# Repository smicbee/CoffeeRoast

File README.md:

# CoffeeRoast

We built a coffee roaster from a popcorn machine by adding temperature control. It follows a reproducible roast curve.

## Used Components

**Microcontroller:** LilyGo T-Display S3 ESP32-S3 (probably overkill, but it has a nice display and WiFi functionality if needed)  
From: [Amazon](https://www.amazon.de/LILYGO-T-Display-S3-Entwicklungsboard-Normalbildschirm-schwarzem/dp/B0BRTT727Z?source=ps-sl-shoppingads-lpcontext&ref_=fplfs&smid=ANWK9D8XV9DLB&th=1)

**Popcorn Maker:** [Severin Popcorn-Maker](https://popcorn-rezepte.de/severin-pc-3751-popcornautomat-weiss-heissluft)  
From: Ebay/Kleinanzeigen for 5-10€. People often get this as a gift, use it once or not at all, and then sell it on eBay.

**Temperature Sensor:** MAX6675 Temperature Sensor, K Type  
From: [Amazon](https://www.amazon.de/dp/B0DFM7SJ3Z?ref=ppx_yo2ov_dt_b_fed_asin_title)

**Solid State Relay:** Solid-State-Relay SSR-40DA  
From: [Amazon](https://www.amazon.de/dp/B0CDKCBJRT?ref=ppx_yo2ov_dt_b_fed_asin_title)

Cables, drills, screwdriver, soldering iron

## Instructions

To modify the roaster, we had to:
* Add a temperature sensor
* Add a solid-state relay to the heater
* Add a PWM transistor to the fan

First, we took apart the popcorn maker. It basically consists of two elements: heating coils and a fan for the air.  
These popcorn makers are engineered to the limit, so please be gentle with them as they are made of a lot of plastic. We destroyed a couple until we got it right. Even then, the plastic melted on the third continuous roast.

The main power switch connects the 230V from the outlet directly to the heating coils. The fan is connected to the heating coil in a way that ~24V AC goes through a rectifier (4 diodes) and is converted from AC to DC.

In the first step, we needed to decouple the heating coils from the fan and make the heating coil controllable using our solid-state relay. We disconnected the fan from the diodes so we could run it from an external power supply providing 24V later on.  
The heating coil was then soldered directly to the neutral conductor (blue wire). The red wire was cut, and the solid-state relay was installed in between so we could control the power of the heating element using PWM later.

An external or lab power supply was used to provide 24V DC to the fan, so it runs permanently. The fan can take from 4V to 30V. We can adjust the voltage to control the speed or later use a GPIO, a diode, and a transistor to control it from the ESP32. The ESP ensures a smooth start of the fan. We broke one of the fans due to rapid spin up/down.

We drilled a hole in the top metal container to fit the thermocouple inside the roasting chamber.  
**Note:** If the temperature sensor touches the metal casing, it won't work properly. We insulated the sensor with Kapton tape or a non-conductive washer. The temperature reading is 0°C if the motor is spinning and no insulation was used. This is handled by the code to be filtered out, but the roaster will go into fail-safe mode after 30s of nonsensical temperature readings and spin up the fan to 100%.

The other 4 pins go into the ESP32 (VCC = 5V, GND = Ground, CLK = GPIO_13, CS = GPIO_12, DO = GPIO_11).

Also, the solid-state relay is connected to the ESP32. In our case, the voltage provided by the GPIO was sufficient to control the solid-state relay, so we controlled it directly via the GPIO. If this does not work, you will need a separate transistor and a 5V supply for the SSR.  
The SSR uses GPIO_1 in our setup.

## Control Box

We 3D printed a box containing:
* ESP32
* 24V Fan PWM control
* SSR (solid-state relay) control
* Temperature sensor readout board

And that's it!

Initially, we wanted to use the ESP32 with Artisan (the software used for commercial products, e.g., Coffeelogic Nano), but we had no luck getting it to work with a PID. So, we decided to write our own software using C#. Communication is done via simple serial commands.  
You can send "get temp" via serial to the ESP32, and it will respond with the current temperature from the thermocouple.  
You can also send "set setpoint 255", which the ESP32 interprets to set the PWM duty cycle to 100% (255 = 100%, 128 = 50%, 0 = 0%).  
The firmware clamps `set setpoint` and `set fan` commands to the 0-255 PWM range and supports `get status` for a compact controller health line with state, temperature, heater, fan, fan target, and thermocouple error count.
The C# application can be found in the iRoastControl folder.

# Example Usage

Use no more than 100g of beans and roast in a well-ventilated area. Prepare for coffee skins flying _everywhere_.  
You can stop the roast at any time by flipping the on-off switch, which effectively disconnects the heater while keeping the cooling fan running.

[12s_roast.webm](https://github.com/user-attachments/assets/c60a7ab9-1068-4cd1-9d56-9880ee272cc1)

[12s video of 12min roasting](docu/assets/img/rel/12s_roast.webm)

# CoffeeRoast V2 Web

Die neue Steuerungsoberfläche liegt unter [`CoffeeRoast V2/`](CoffeeRoast%20V2/) und ist als moderne, responsive Webanwendung umgesetzt.

- Live-Verbindung zum bestehenden ESP32 über die Web Serial API
- vorhandenes serielles Protokoll und alle `.kpro`-Rezepte bleiben nutzbar
- Safety-Preflight, Failsafe, Vorheizen, Rösten und Abkühlen
- eingebauter Simulator, Canvas-Live-Plot und CSV-Export
- öffentlich bereitgestellt unter **https://coffeeroast.michaelbeetz.de/**

Für die USB-Verbindung wird Chrome oder Edge benötigt. Der Browser spricht direkt mit dem lokal ausgewählten USB-Gerät; der Webserver erhält keinen Zugriff auf den Controller.

# iRoastControl (Legacy)

iRoastControl is the control software. It comes with predefined roast curves you can use for your first roast.

## Build and Run on Windows

iRoastControl is a Windows Forms application for .NET Framework 4.7.2. Build it with Visual Studio 2022 and the ".NET desktop development" workload installed, including the .NET Framework 4.7.2 targeting pack or developer pack.

1. Connect the ESP32 roaster controller to the Windows PC over USB and confirm it appears as a COM port.
2. Open `iRoastControl Software/iRoastControl.sln` in Visual Studio.
3. Restore NuGet packages when Visual Studio prompts you, or use **Build > Restore NuGet Packages** before the first build. The project uses `packages.config`, so packages are restored into a repository-level `packages` folder.
4. Build the `Debug|Any CPU` or `Release|Any CPU` configuration, then press **Start** in Visual Studio or run the generated `iRoastControl.exe` from `iRoastControl Software/bin/Debug/` or `iRoastControl Software/bin/Release/`.

On startup the application scans available COM ports at `115200` baud, 8 data bits, no parity, one stop bit, and no handshake. It sends `hello` and expects the ESP32 firmware to answer `popcorn roaster`; after that it sends commands such as `get temp`, `set setpoint <0-255>`, and `set fan <0-255>`. If the app does not connect, check that the ESP32 firmware is running, no serial monitor has the port open, and the USB driver exposes the board as a COM port.

Roast recipes are loaded from the `Recipes` folder next to the running application. The source recipes live in `iRoastControl Software/Recipes/*.kpro` and are copied to the build output during the Visual Studio build. Add custom `.kpro` files to that folder before building, or copy them into `bin/Debug/Recipes/` or `bin/Release/Recipes/` beside the executable.

## First-Run Calibration and Safety Check

Before the first heated run, flash the ESP32 firmware, start iRoastControl, and leave the chamber empty. When you press "Run" from idle, the application requests `get status` from the controller and shows a preflight checklist. Confirm only after the thermocouple is insulated from the metal chamber, the fan moves air freely, the SSR is wired through the controller, ventilation is running, and the manual power cut-off is reachable.

Each roasting curve has three phases: pre-heating, running, and cool-down. When you click "Run" the first time, the application pre-heats the empty popcorn machine until the thermocouple reaches 180°C. This is when you add your coffee beans. After that, press "Run" again and the button will turn yellow. This is where the roasting curve starts. You can follow your roasting temperatures by watching the red graph. Pressing the "Run" button again will abort and start the cool-down phase, where the heating element turns off and only the fan runs. When the temperature drops below 60°C, the app returns to idle.

If the thermocouple returns repeated impossible readings, the firmware enters failsafe, turns the heater off, and drives the fan to 255/255. The app also treats a controller status containing `failsafe` as a blocked start until the wiring or sensor issue is fixed.

## UI

At the moment, the curves are defined by some points in the source code, which get interpolated using a CubicSpline function. You can find the key points in `ControlClass.cs` in the function `generateDefaultCurve()`. Each point describes the temperature depending on the time in seconds, e.g., `targetPoints.Add(new PointF(660, 180));` means at 660s of the roasting curve, we should reach 180°C.  
Adjust as you like.

# Fails

If the popcorn maker is old (like 20 years), the fan blades are rather brittle and may break easily if used on full power.

**Note:** If the temperature sensor touches the metal casing, it won't work properly. We recommend insulating the sensor with Kapton tape or a non-conductive washer.

# Tips

* Cover any holes on top with Kapton tape to retain heat better. Plastic might melt a bit, though.
* Test the roast with actual popcorn, as it's cheaper if anything goes wrong.
* Experiment and change only one setting at a time.

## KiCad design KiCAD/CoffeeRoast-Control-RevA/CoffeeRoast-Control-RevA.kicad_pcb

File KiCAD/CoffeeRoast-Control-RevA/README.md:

# CoffeeRoast-Control RevA.1 PCB Draft

This is the generated RevA.1 hardware draft for moving the CoffeeRoast electronics onto a PCB. The current board has been updated with the agreed robustness optimizations and has zero KiCad error-level DRC violations, but it still needs manual engineering review before fabrication.

## Design decision captured from chat

- Use **one 230V appliance inlet for the whole roaster enclosure**.
- Inside the enclosure use a **certified isolated 230VAC -> 24VDC / 3A PSU**.
- The controller PCB itself is **low-voltage only** and accepts the PSU's 24VDC output.
- The PCB generates 5V via a buck module and 3.3V via a RevA.1 switching-regulator footprint/selection for the ESP32-S3 module.
- The heater's 230V path is still switched by an **external SSR module with heatsink**; 230V is intentionally not routed on this PCB.
- RevA.1 adds low-voltage robustness features: input bulk capacitor, 24V input TVS, fan TVS, USB ESD footprint, thermocouple filter footprint, and rail test pads.

## Files

- `CoffeeRoast-Control-RevA.kicad_pcb` — KiCad board draft with real on-board USB-C footprint and autorouted/manual-cleanup tracks.
- `CoffeeRoast-Control-RevA.kicad_sch` — vollständiger, editierbarer KiCad-Schaltplan mit Funktionsblöcken für Versorgung, Lüfter/SSR, ESP32, MAX6675, USB und Testzugänge; die benannten Netze entsprechen dem gerouteten PCB.
- `tools/generate_full_schematic.py` — reproduzierbarer Generator für den Schaltplanentwurf; die native `.kicad_sch`-Datei wurde mit KiCad 9 konvertiert und geprüft.
- `render/schematic/CoffeeRoast-Control-RevA.pdf` und `.svg` — exportierte Schaltplanansichten; `render/schematic/erc.json` enthält den aktuellen ERC-Bericht.
- `docs/netlist.csv` — tabellarische Referenz der beabsichtigten elektrischen Verbindungen.
- `docs/bom.csv` — Stückliste des aktuellen PCB-Entwurfs.
- `docs/esp32_debug_pads.csv` — ESP32-S3 TPESP1-40 tiny probe pad mapping.
- `docs/esp32_solder_pads.csv` — larger labeled bottom-side PADESP1-40 solder pad mapping for attaching wires later.
- `docs/routing_notes.md` — routing/DRC status and fabrication caveats.
- `docs/reva1_optimizations.md` — RevA.1 robustness changes and what was deliberately left for RevB.
- `tools/apply_reva1_optimizations.py` — idempotent pcbnew script that applies the RevA.1 PCB additions.
- `production/partial-smd-pcba/` — generated Gerber/drill + partial SMD assembly BOM/CPL package for first prototype ordering.
- `tools/prepare_partial_pcba_package.py` — regenerates the partial-SMD PCBA handoff package.
- `symbols/` and `footprints.pretty/` — local ESP32-S3-WROOM-1 and USB-C library files copied from KiCad upstream.

## Firmware pin mapping preserved

| Function | ESP32-S3-WROOM-1 pin | GPIO | Firmware variable |
|---|---:|---:|---|
| Heater/SSR PWM | 39 | GPIO1 | `relayPin` |
| Fan PWM | 38 | GPIO2 | `fanPin` |
| MAX6675 DO/SO | 19 | GPIO11 | `thermoDO` |
| MAX6675 CS | 20 | GPIO12 | `thermoCS` |
| MAX6675 CLK/SCK | 21 | GPIO13 | `thermoCLK` |
| USB D- | 13 | native USB D- | serial/flash |
| USB D+ | 14 | native USB D+ | serial/flash |
| BOOT | 27 | GPIO0 | flash mode |
| EN/RESET | 3 | EN | reset |

## ESP32 debug pads

All ESP32-S3-WROOM-1 side pins 1-40 are exposed twice: tiny local probe pads named `TPESP1` through `TPESP40` around U1, and larger labeled bottom-side solder pads named `PADESP1` through `PADESP40` routed outward for attaching wires later. The mappings are in `docs/esp32_debug_pads.csv` and `docs/esp32_solder_pads.csv`. These include the spare GPIOs plus already-used signals such as USB D+/D-, MAX6675 SPI, BOOT/EN, fan PWM, heater/SSR PWM, 3V3, and GND.

## Power tree

```text
230VAC inlet in enclosure
  +--> certified 230VAC -> 24VDC / 3A PSU
          +--> J1 on this PCB
                +--> C4 input bulk + D2 24V TVS protection
                +--> F1 24V-side fuse placeholder
                +--> J2 24V fan via Q1 low-side MOSFET + D1/D3 fan clamp
                +--> U4 24V -> 5V buck module
                        +--> SSR input driver supply
                        +--> U3 3.3V switching regulator selection
                                +--> ESP32-S3-WROOM-1 + MAX6675

230VAC heater line: external SSR module only, not on this PCB.
```

## Important limitations before fabrication

This board now loads in KiCad 9 and has been routed/checked headlessly. KiCad error-level DRC is clean, but before ordering boards:

1. Open the project in KiCad.
2. Replace remaining generic placeholders with exact sourced parts: fuse holder, U3 switching regulator footprint, U4 buck module, TVS packages, USB ESD package, MOSFET/regulator variants. J1-J4 are deliberately large hand-solder pads now, not PCBA connector placements.
3. Re-run ERC/DRC after any mechanical/footprint changes.
4. Confirm ESP32-S3-WROOM-1 antenna keepout has no copper and is at board edge.
5. Confirm the fan path, D3 TVS choice, Q1 MOSFET, and hand-solder pad/wire strain-relief scheme are rated for the real 24V/2.5A fan current.
6. Confirm J5 enclosure cutout/edge placement for the exact USB-C part and replace U5 with an exact USB2 ESD footprint.
7. Review USB CC pulldowns: R10/R11 = 5.1k to GND, VBUS is sense-only.
8. Decide whether C5 should be populated after thermocouple noise testing; leave DNP if it biases readings.
9. Review mains wiring separately: fused IEC inlet, PE/strain relief, certified 24V PSU, external SSR heatsink, thermal cut-off.

## RevB candidates

- Replace the generic U4 buck module with an integrated switch-mode converter.
- Add reverse-polarity ideal-diode/P-MOSFET input protection if final wiring risk justifies the extra footprint/reroute.
- Add current/thermal sensing for fan/heater diagnostics.

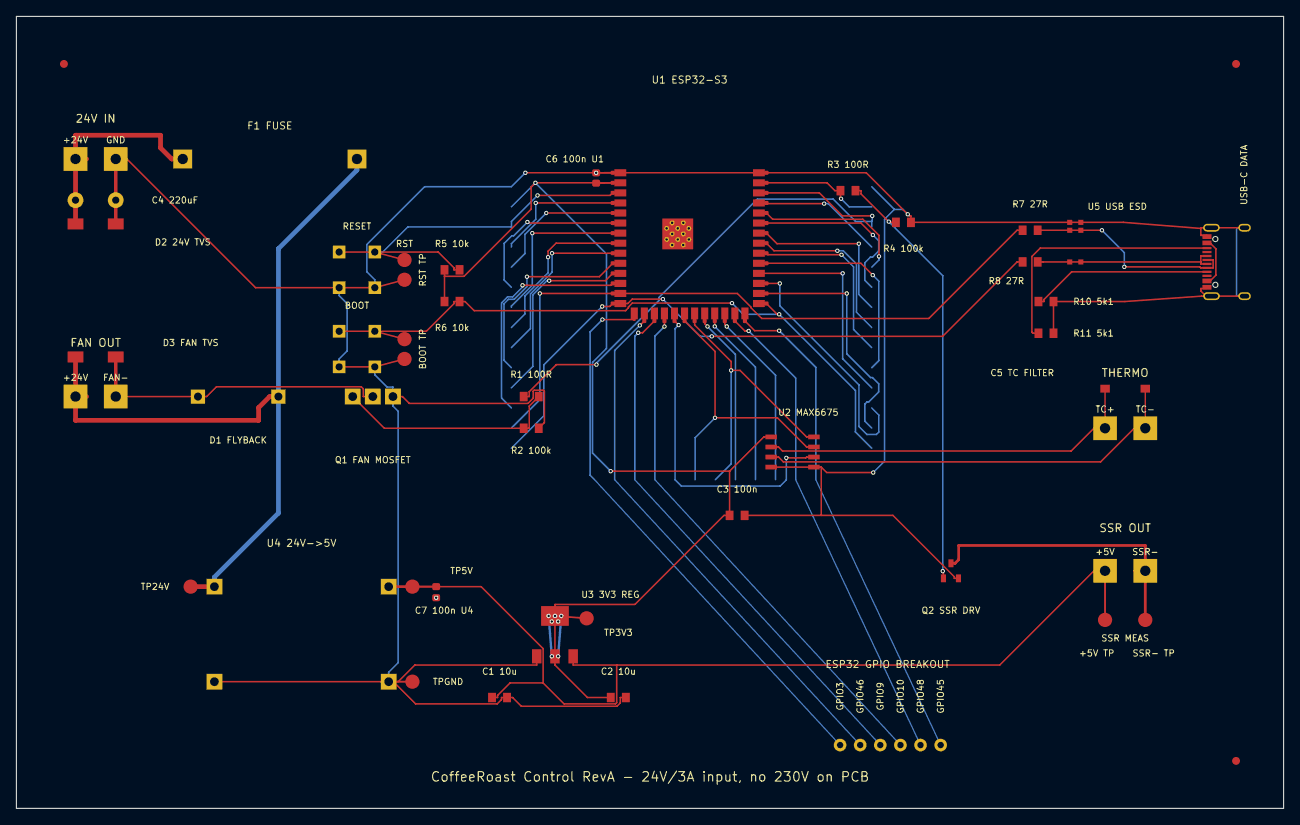
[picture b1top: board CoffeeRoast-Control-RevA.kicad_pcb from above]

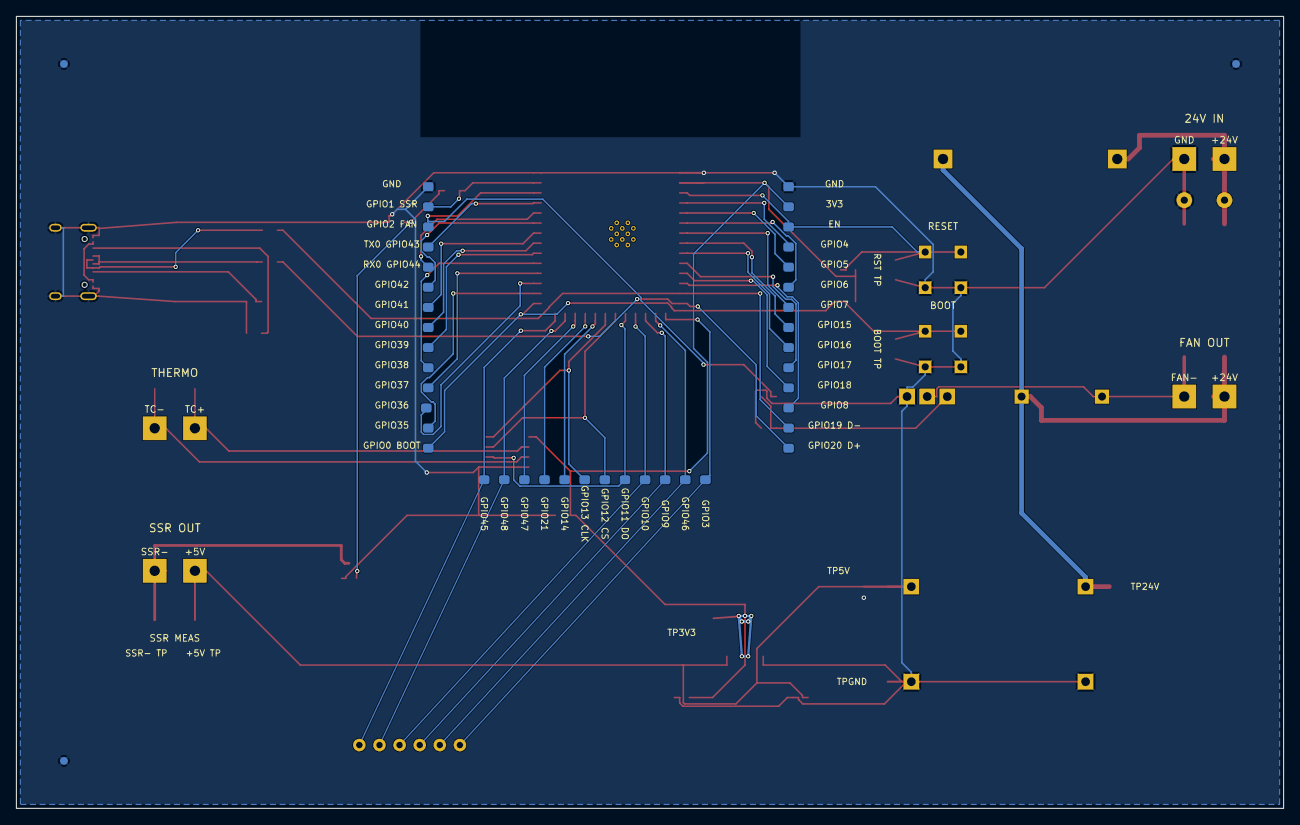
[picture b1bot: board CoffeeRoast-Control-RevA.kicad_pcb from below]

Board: 2 copper layers, 160.0 x 100.0 mm, 129 parts (43 on the bottom side), 53 nets.

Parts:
C1: 10uF_5V
C2: 10uF_3V3
C3: 100nF_MAX6675
C4: 220uF_35V_INPUT_BULK
C5: 1nF_C0G_THERMO_DIFF_FILTER_DNP_IF_NOISY
C6: 100nF_U1_DECOUPLING_0603
C7: 100nF_U4_OUTPUT_DECOUPLING_0603
D1: SB560_FLYBACK
D2: SMBJ33A_24V_INPUT_TVS
D3: SMBJ33A_FAN_TVS
F1: T3.15A_24V_SIDE
FID1, FID2, FID3, FID4, FID5, FID6: FIDUCIAL_GLOBAL_1MM
J1: 24V_IN_FROM_230V_PSU_3A
J2: FAN_24V_PWM_3A
J3: SSR_INPUT_TO_EXTERNAL_SSR
J4: K_TYPE_THERMOCOUPLE
J5: USB_C_Receptacle_XKB_U262-16XN-4BVC11
JGPIO1: ESP32_GPIO_BREAKOUT_ROW
PADESP1, PADESP40: GND
PADESP2: 3V3
PADESP3: EN
PADESP4: IO4
PADESP5: IO5
PADESP6: IO6
PADESP7: IO7
PADESP8: IO15
PADESP9: IO16
PADESP10: IO17
PADESP11: IO18
PADESP12: IO8
PADESP13: USB_D-
PADESP14: USB_D+
PADESP15: IO3
PADESP16: IO46
PADESP17: IO9
PADESP18: IO10
PADESP19: IO11
PADESP20: IO12
PADESP21: IO13
PADESP22: IO14
PADESP23: IO21
PADESP24: IO47
PADESP25: IO48
PADESP26: IO45
PADESP27: IO0
PADESP28: IO35
PADESP29: IO36
PADESP30: IO37
PADESP31: IO38
PADESP32: IO39
PADESP33: IO40
PADESP34: IO41
PADESP35: IO42
PADESP36: RXD0
PADESP37: TXD0
PADESP38: IO2
PADESP39: IO1
Q1: IRLB8721_OR_3V3_LOGIC_NMOS_RDS_ON_LOW
Q2: 2N7002_SSR_DRIVER
R1, R3: 100R
R2, R4: 100k
R5: 10k_EN_PULLUP
R6: 10k_BOOT_PULLUP
R7: 27R_USB_DN
R8: 27R_USB_DP
R10: 5k1_CC1_RD
R11: 5k1_CC2_RD
SW1: RESET_EN
SW2: BOOT
TP3V3: +3V3_TEST
TP5V: +5V_TEST
TP24V: +24V_FUSED_TEST
TPBOOT1: BOOT_TWEEZER_PADS
TPESP1, TPESP40: GND
TPESP2: 3V3
TPESP3: EN
TPESP4: IO4
TPESP5: IO5
TPESP6: IO6
TPESP7: IO7
TPESP8: IO15
TPESP9: IO16
TPESP10: IO17
TPESP11: IO18
TPESP12: IO8
TPESP13: USB_D-/IO19
TPESP14: USB_D+/IO20
TPESP15: IO3
TPESP16: IO46
TPESP17: IO9
TPESP18: IO10
TPESP19: IO11/MAXDO
TPESP20: IO12/MAXCS
TPESP21: IO13/MAXCLK
TPESP22: IO14
TPESP23: IO21
TPESP24: IO47
TPESP25: IO48
TPESP26: IO45
TPESP27: IO0/BOOT
TPESP28: IO35
TPESP29: IO36
TPESP30: IO37
TPESP31: IO38
TPESP32: IO39
TPESP33: IO40
TPESP34: IO41
TPESP35: IO42
TPESP36: RXD0/IO44
TPESP37: TXD0/IO43
TPESP38: IO2/FAN
TPESP39: IO1/SSR
TPGND: GND_TEST
TPRESET1: RESET_TWEEZER_PADS
TPSSR1: SSR_OUT_MEAS_PADS
U1: ESP32-S3-WROOM-1
U2: MAX6675_SOIC8_3V3
U3: 3V3_SWITCHING_REGULATOR_>=600mA_5V_IN_REPLACES_AM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
U4: 24V_TO_5V_BUCK_MODULE_>=1A_LOW_NOISE
U5: USBLC6-2SC6_OR_USB2_ESD

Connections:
+3V3: C2.1, C3.1, C6.1, PADESP2.1, R5.1, R6.1, TP3V3.1, TPESP2.1, U1.2, U2.4, U3.2
+5V: C1.1, C7.1, J3.1, TP5V.1, TPSSR1.1, U3.3, U4.3
+24V_FUSED: D1.2, D3.1, F1.2, J2.1, TP24V.1, U4.1
+24V_RAW: C4.1, D2.1, F1.1, J1.1
BOOT: PADESP27.1, R6.2, SW2.1, SW2.2, TPBOOT1.1, TPESP27.1, U1.27
EN: PADESP3.1, R5.2, SW1.1, SW1.2, TPESP3.1, TPRESET1.1, U1.3
FAN_GATE: Q1.1, R1.2, R2.1
FAN_NEG: D1.1, D3.2, J2.2, Q1.2
FAN_PWM: PADESP38.1, R1.1, TPESP38.1, U1.38
GND: C1.2, C2.2, C3.2, C4.2, C6.2, C7.2, D2.2, FID4.1, FID5.1, FID6.1, J1.2, J5.A1, J5.A12, J5.B1, J5.B12, J5.S1, PADESP1.1, PADESP40.1, Q1.3, Q2.2, R2.2, R4.2, R10.2, R11.2, SW1.3, SW1.4, SW2.3, SW2.4, TPBOOT1.2, TPESP1.1, TPESP40.1, TPGND.1, TPRESET1.2, U1.1, U1.40, U2.1, U2.8, U3.1, U4.2, U4.4, U5.3, U5.4
GPIO3: JGPIO1.1, PADESP15.1, TPESP15.1, U1.15
GPIO4: PADESP4.1, TPESP4.1, U1.4
GPIO5: PADESP5.1, TPESP5.1, U1.5
GPIO6: PADESP6.1, TPESP6.1, U1.6
GPIO7: PADESP7.1, TPESP7.1, U1.7
GPIO8: PADESP12.1, TPESP12.1, U1.12
GPIO9: JGPIO1.3, PADESP17.1, TPESP17.1, U1.17
GPIO10: JGPIO1.4, PADESP18.1, TPESP18.1, U1.18
GPIO14: PADESP22.1, TPESP22.1, U1.22
GPIO15: PADESP8.1, TPESP8.1, U1.8
GPIO16: PADESP9.1, TPESP9.1, U1.9
GPIO17: PADESP10.1, TPESP10.1, U1.10
GPIO18: PADESP11.1, TPESP11.1, U1.11
GPIO21: PADESP23.1, TPESP23.1, U1.23
GPIO35: PADESP28.1, TPESP28.1, U1.28
GPIO36: PADESP29.1, TPESP29.1, U1.29
GPIO37: PADESP30.1, TPESP30.1, U1.30
GPIO38: PADESP31.1, TPESP31.1, U1.31
GPIO39: PADESP32.1, TPESP32.1, U1.32
GPIO40: PADESP33.1, TPESP33.1, U1.33
GPIO41: PADESP34.1, TPESP34.1, U1.34
GPIO42: PADESP35.1, TPESP35.1, U1.35
GPIO45: JGPIO1.6, PADESP26.1, TPESP26.1, U1.26
GPIO46: JGPIO1.2, PADESP16.1, TPESP16.1, U1.16
GPIO47: PADESP24.1, TPESP24.1, U1.24
GPIO48: JGPIO1.5, PADESP25.1, TPESP25.1, U1.25
HEATER_PWM: PADESP39.1, R3.1, TPESP39.1, U1.39
MAX_CS: PADESP20.1, TPESP20.1, U1.20, U2.6
MAX_DO: PADESP19.1, TPESP19.1, U1.19, U2.7
MAX_SCK: PADESP21.1, TPESP21.1, U1.21, U2.5
RXD0_GPIO44: PADESP36.1, TPESP36.1, U1.36
SSR_GATE: Q2.1, R3.2, R4.1
SSR_NEG: J3.2, Q2.3, TPSSR1.2
THERMO_MINUS: C5.2, J4.2, U2.2
THERMO_PLUS: C5.1, J4.1, U2.3
TXD0_GPIO43: PADESP37.1, TPESP37.1, U1.37
USB_CC1: J5.A5, R10.1
USB_CC2: J5.B5, R11.1
USB_DN: J5.A7, J5.B7, R7.2, U5.1, U5.6
USB_DN_MCU: PADESP13.1, R7.1, TPESP13.1, U1.13
USB_DP: J5.A6, J5.B6, R8.2, U5.2, U5.5
USB_DP_MCU: PADESP14.1, R8.1, TPESP14.1, U1.14
USB_VBUS: J5.A4, J5.A9, J5.B4, J5.B9

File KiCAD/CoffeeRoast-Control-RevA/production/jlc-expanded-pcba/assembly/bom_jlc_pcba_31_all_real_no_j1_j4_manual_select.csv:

Comment,Designator,Footprint,LCSC Part #
10uF_5V,C1,0805,C15850
10uF_3V3,C2,0805,C15850
100nF_MAX6675,C3,0805,C49678
100nF_U1_DECOUPLING_0603,C6,0603,C14663
100nF_U4_OUTPUT_DECOUPLING_0603,C7,0603,C14663
USB_C_Receptacle_XKB_U262-16XN-4BVC11,J5,USB-C receptacle XKB U262-16XN,C319148
2N7002_SSR_DRIVER,Q2,SOT-23,C8545
100R,R1,0805,C17408
100k,R2,0805,C149504
100R,R3,0805,C17408
100k,R4,0805,C149504
10k_EN_PULLUP,R5,0805,C17414
10k_BOOT_PULLUP,R6,0805,C17414
27R_USB_DN,R7,0805,C17594
27R_USB_DP,R8,0805,C17594
5k1_CC1_RD,R10,0805,C27834
5k1_CC2_RD,R11,0805,C27834
ESP32-S3-WROOM-1,U1,ESP32-S3-WROOM-1 module,C2913201
MAX6675_SOIC8_3V3,U2,SOIC-8,C16030
1nF_C0G_THERMO_DIFF_FILTER_DNP_IF_NOISY,C5,0805 candidate / VERIFY current footprint,C76625
SB560_FLYBACK,D1,DO-201AD / VERIFY,C139684
SMBJ33A_24V_INPUT_TVS,D2,SMB / VERIFY current footprint,C135067
SMBJ33A_FAN_TVS,D3,SMB / VERIFY current footprint,C135067
IRLB8721_OR_3V3_LOGIC_NMOS_RDS_ON_LOW,Q1,TO-220 / VERIFY,C153222
RESET_EN,SW1,6x6mm THT tactile / VERIFY,C92655
BOOT,SW2,6x6mm THT tactile / VERIFY,C92655
24V_TO_5V_BUCK_MODULE_>=1A_LOW_NOISE,U4,Pololu/module candidate / VERIFY footprint,C26689857
USBLC6-2SC6_OR_USB2_ESD,U5,SOT-23-6 candidate / VERIFY current custom footprint,C7519
220uF_35V_INPUT_BULK,C4,Radial electrolytic / manual select,
T3.15A_24V_SIDE,F1,5x20mm fuse holder / manual select,
3V3_SWITCHING_REGULATOR_>=600mA_5V_IN_REPLACES_AMS1117,U3,Switching regulator module / manual select,

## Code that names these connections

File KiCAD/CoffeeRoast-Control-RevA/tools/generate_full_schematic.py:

#!/usr/bin/env python3
"""Generate the editable CoffeeRoast RevA.1 legacy KiCad schematic source.

KiCad opens this v4 file and converts it to the native .kicad_sch format on save.
The schematic mirrors the routed PCB's named nets; 230 VAC remains explicitly off-board.
"""
from pathlib import Path

ROOT = Path(__file__).resolve().parents[1]
OUT = Path("/tmp/CoffeeRoast-Control-RevA-generated.sch")
items=[]
uid=0x65000000

def comp(lib, ref, value, x, y, orient=(1,0,0,-1), footprint=""):
    global uid
    uid += 1
    a,b,c,d=orient
    items.extend([
        "$Comp", f"L {lib} {ref}", f"U 1 1 {uid:X}", f"P {x} {y}",
        f'F 0 "{ref}" H {x+150} {y+100} 50  0000 C CNN',
        f'F 1 "{value}" H {x+250} {y-100} 50  0000 C CNN',
        f'F 2 "{footprint}" H {x} {y} 50  0001 C CNN',
        f"\t1    {x} {y}", f"\t{a}    {b}    {c}    {d}", "$EndComp"
    ])

def label(x,y,name,orient=0):
    items.append(f"Text Label {x} {y} {orient}    40   ~ 0\n{name}")

def wire(x1,y1,x2,y2): items.append(f"Wire Wire Line\n\t{x1} {y1} {x2} {y2}")
def note(x,y,text,size=60): items.append(f'Text Notes {x} {y} 0    {size}   ~ 12\n{text}')
def box(x1,y1,x2,y2): items.append(f"Wire Notes Line\n\t{x1} {y1} {x2} {y1}\nWire Notes Line\n\t{x2} {y1} {x2} {y2}\nWire Notes Line\n\t{x2} {y2} {x1} {y2}\nWire Notes Line\n\t{x1} {y2} {x1} {y1}")

def two_pin_h(lib,ref,value,x,y,left,right,fp=""):
    # R/Fuse are vertical by default; switches are horizontal by default.
    if lib in {"Device:R","Device:Fuse"}:
        comp(lib,ref,value,x,y,(0,-1,-1,0),fp); off=150
    elif lib == "Switch:SW_Push":
        comp(lib,ref,value,x,y,(1,0,0,-1),fp); off=200
    else:
        comp(lib,ref,value,x,y,(1,0,0,-1),fp); off=150
    wire(x-off,y,x-off-50,y); label(x-off-50,y,left)
    wire(x+off,y,x+off+50,y); label(x+off+50,y,right,2)

def two_pin_v(lib,ref,value,x,y,top,bottom,fp=""):
    # R/C are vertical by default; diodes are horizontal and rotated here.
    orient=(1,0,0,-1) if lib in {"Device:R","Device:C","Device:C_Polarized"} else (0,-1,-1,0)
    comp(lib,ref,value,x,y,orient,fp); off=150
    wire(x,y-off,x,y-off-50); label(x,y-off-50,top,1)
    wire(x,y+off,x,y+off+50); label(x,y+off+50,bottom,1)

def conn1(ref,value,x,y,n,nets,fp=""):
    comp(f"Connector_Generic:Conn_01x{n:02d}",ref,value,x,y,(1,0,0,-1),fp)
    start=y-((n-1)//2)*100
    for i,net in enumerate(nets):
        py=start+i*100; wire(x-200,py,x-250,py); label(x-250,py,net)

def conn2x20(ref,value,x,y,nets,fp=""):
    comp("Connector_Generic:Conn_02x20_Odd_Even",ref,value,x,y,(1,0,0,-1),fp)
    used={"GND","+3V3","EN","USB_DN_MCU","USB_DP_MCU","GPIO3","GPIO46","GPIO9","GPIO10","MAX_DO","MAX_CS","MAX_SCK","GPIO48","GPIO45","BOOT","FAN_PWM","HEATER_PWM"}
    start=y-900
    for pin in range(1,41):
        py=start+((pin-1)//2)*100
        px=x-200 if pin%2 else x+300
        if nets[pin-1] not in used:
            items.append(f"NoConn ~ {px} {py}")
        elif pin%2:
            wire(px,py,x-250,py); label(x-250,py,nets[pin-1])
        else:
            wire(px,py,x+350,py); label(x+350,py,nets[pin-1],2)

# Title and explicit safety boundary
note(600,550,"COFFEEROAST CONTROL RevA.1 — LOW-VOLTAGE CONTROLLER",100)
note(600,760,"230 VAC IS OFF-BOARD: certified 230VAC→24VDC PSU + external SSR/heatsink + thermal cutoff",55)

# 24 V input and power conversion
box(500,950,3900,2750); note(650,1120,"POWER INPUT / PROTECTION / CONVERSION",70)
conn1("J1","24V_IN_FROM_CERTIFIED_PSU",900,1550,2,["+24V_RAW","GND"])
two_pin_h("Device:Fuse","F1","T3.15A_24V_SIDE",1600,1450,"+24V_RAW","+24V_FUSED")
two_pin_v("Device:C_Polarized","C4","220uF_35V",1250,2050,"+24V_RAW","GND")
two_pin_v("Device:D_TVS","D2","SMBJ33A_INPUT_TVS",1650,2050,"GND","+24V_RAW")
conn1("U4","24V_TO_5V_BUCK_MODULE",2350,1600,4,["+24V_FUSED","GND","+5V","GND"])
two_pin_v("Device:C","C7","100nF_U4_OUT",2750,2100,"+5V","GND")
conn1("U3","3V3_SWITCHING_REGULATOR",3250,1600,3,["GND","+3V3","+5V"])
two_pin_v("Device:C","C1","10uF_5V",3100,2200,"+5V","GND")
two_pin_v("Device:C","C2","10uF_3V3",3550,2200,"+3V3","GND")

# Fan and SSR output stages
box(4200,950,7350,2750); note(4350,1120,"FAN + EXTERNAL SSR DRIVERS",70)
conn1("J2","24V_FAN_OUTPUT",4550,1500,2,["+24V_FUSED","FAN_NEG"])
two_pin_h("Device:R","R1","100R",5200,1350,"FAN_PWM","FAN_GATE")
two_pin_v("Device:R","R2","100k_GATE_PULLDOWN",5500,1900,"FAN_GATE","GND")
conn1("Q1","3V3_LOGIC_NMOS_FAN_GDS",6000,1550,3,["FAN_GATE","FAN_NEG","GND"])
two_pin_v("Device:D","D1","SB560_FLYBACK",6500,1550,"+24V_FUSED","FAN_NEG")
two_pin_v("Device:D_TVS","D3","SMBJ33A_FAN_TVS",6900,1550,"FAN_NEG","+24V_FUSED")
conn1("J3","EXTERNAL_SSR_INPUT",4550,2350,2,["+5V","SSR_NEG"])
two_pin_h("Device:R","R3","100R",5200,2250,"HEATER_PWM","SSR_GATE")
two_pin_v("Device:R","R4","100k_GATE_PULLDOWN",5500,2450,"SSR_GATE","GND")
conn1("Q2","2N7002_SSR_DRIVER_GDS",6000,2350,3,["SSR_GATE","GND","SSR_NEG"])
note(6250,2520,"SSR input only — no mains on PCB",45)

# ESP32 module and reset/boot
box(7600,950,11200,4400); note(7750,1120,"ESP32-S3-WROOM-1 CONTROLLER",70)
u1nets=["GND","+3V3","EN","GPIO4","GPIO5","GPIO6","GPIO7","GPIO15","GPIO16","GPIO17","GPIO18","GPIO8","USB_DN_MCU","USB_DP_MCU","GPIO3","GPIO46","GPIO9","GPIO10","MAX_DO","MAX_CS","MAX_SCK","GPIO14","GPIO21","GPIO47","GPIO48","GPIO45","BOOT","GPIO35","GPIO36","GPIO37","GPIO38","GPIO39","GPIO40","GPIO41","GPIO42","RXD0_GPIO44","TXD0_GPIO43","FAN_PWM","HEATER_PWM","GND"]
conn2x20("U1","ESP32-S3-WROOM-1",9300,2450,u1nets,"RF_Module:ESP32-S3-WROOM-1")
two_pin_v("Device:C","C6","100nF_U1_DECOUPLING",10800,1500,"+3V3","GND")
two_pin_h("Device:R","R5","10k_EN_PULLUP",8000,3500,"+3V3","EN")
two_pin_h("Switch:SW_Push","SW1","RESET",8500,3750,"EN","GND")
two_pin_h("Device:R","R6","10k_BOOT_PULLUP",9600,3500,"+3V3","BOOT")
two_pin_h("Switch:SW_Push","SW2","BOOT",10100,3750,"BOOT","GND")
conn1("JGPIO1","SPARE_GPIO_BREAKOUT",10800,3300,6,["GPIO3","GPIO46","GPIO9","GPIO10","GPIO48","GPIO45"])

# Thermocouple interface
box(500,3000,3900,5000); note(650,3170,"K-TYPE THERMOCOUPLE / MAX6675",70)
conn1("J4","K_TYPE_THERMOCOUPLE",900,3900,2,["THERMO_PLUS","THERMO_MINUS"])
two_pin_v("Device:C","C5","1nF_C0G_DNP_IF_BIASED",1450,3900,"THERMO_PLUS","THERMO_MINUS")
conn1("U2","MAX6675_SOIC8_3V3",2550,3900,8,["GND","THERMO_MINUS","THERMO_PLUS","+3V3","MAX_SCK","MAX_CS","MAX_DO","GND"],"Package_SO:SOIC-8_3.9x4.9mm_P1.27mm")
two_pin_v("Device:C","C3","100nF_MAX6675",3300,3900,"+3V3","GND")
note(700,4700,"Firmware: DO=GPIO11, CS=GPIO12, SCK=GPIO13",50)

# USB-C data-only interface and ESD
box(4200,3000,7350,5000); note(4350,3170,"USB-C DATA / FLASH (VBUS SENSE ONLY)",70)
conn1("J5","USB_C_RECEPTACLE_USB2",4550,3950,8,["GND","USB_VBUS","USB_CC1","USB_DP","USB_DN","USB_CC2","USB_VBUS","GND"],"Connector_USB:USB_C_Receptacle_XKB_U262-16XN-4BVC11")
two_pin_v("Device:R","R10","5.1k_CC1_RD",5150,3500,"USB_CC1","GND")
two_pin_v("Device:R","R11","5.1k_CC2_RD",5550,3500,"USB_CC2","GND")
two_pin_h("Device:R","R7","27R_USB_DN",5350,4300,"USB_DN","USB_DN_MCU")
two_pin_h("Device:R","R8","27R_USB_DP",5350,4600,"USB_DP","USB_DP_MCU")
conn1("U5","USBLC6-2SC6_USB_ESD",6500,4050,6,["USB_DN","USB_DP","GND","GND","USB_DP","USB_DN"])
note(4400,4820,"USB VBUS does not power the controller",45)

# Bring-up test points
box(500,5350,7350,6900); note(650,5520,"BRING-UP / TEST ACCESS",70)
for ref,val,x,net in [("TP24V","24V_FUSED",900,"+24V_FUSED"),("TP5V","5V",1500,"+5V"),("TP3V3","3V3",2100,"+3V3"),("TPGND","GND",2700,"GND")]:
    conn1(ref,val,x,6000,1,[net])
conn1("TPRESET1","RESET_TWEEZER",3550,5900,2,["EN","GND"])
conn1("TPBOOT1","BOOT_TWEEZER",4350,5900,2,["BOOT","GND"])
conn1("TPSSR1","SSR_OUT_MEASURE",5150,5900,2,["+5V","SSR_NEG"])
note(650,6500,"TPESP1–40 and PADESP1–40 on PCB mirror U1 pins 1–40; see docs/esp32_debug_pads.csv",45)
note(650,6660,"All named nets here match the routed PCB. Exact U3/U4/U5/Q1/D2/D3 sourced parts remain pre-fabrication review items.",45)

header=["EESchema Schematic File Version 4","LIBS:power","LIBS:device","LIBS:Connector_Generic","LIBS:switch","EELAYER 29 0","EELAYER END","$Descr A3 16535 11693","Sheet 1 1",'Title "CoffeeRoast Control RevA.1"','Date "2026-07-11"','Rev "A.1"','Comp "CoffeeRoast"','Comment1 "Low-voltage controller only; 230 VAC remains off-board"','Comment2 "Generated from routed PCB nets and docs/netlist.csv"',"$EndDescr"]
OUT.write_text("\n".join(header+items+["$EndSCHEMATC",""]),encoding="utf-8")
print(OUT)

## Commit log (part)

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2025-03-27 initial commit^
2025-03-27 Readme added
2025-05-18 added schaltplan.png yw
2025-05-18 added recipes
2025-05-18 readme update
2025-05-18 adjusted some values for more precise roasting
2025-05-31 adding image to readme
2025-05-31 Update README.md
    fixed and typos
2025-05-31 adding image to readme (#1)
    * adding image to readme
    * Update README.md
    fixed and typos
2025-05-31 changes during testing at BK
2025-05-31 add ui screenshot
2025-05-31 adding video
2025-06-01 removed all the typos
2025-06-03 maximum runtime increased to 20min. fixed crash after running out of roasting profile
2025-06-15 adding peanut profile, adding gitignore for visual studio
2025-06-15 button shows state
2025-06-15 commented out debugging lines
2025-06-15 implemented failsafe after 20 error temperature readings
2025-06-15 invalid readings do not contribute to PID
2025-06-15 more debugging options and time multiplicator added
2025-06-16 bugfix
2025-06-18 bugfix. restarting a profile did not work
2025-10-26 Fix roast preparation crashes and improve cooling handling
2026-04-14 project: Updated 'CoffeeRoast'
2026-04-14 ticket: Updated 'Fix control loop timer interval scaling'
2026-04-14 ticket: Updated 'Document how to build and run the Windows control application'
2026-04-17 ticket: Created 'Rework UI' [improvement/high]
2026-04-18 ticket: Updated 'Add bounds checks before writing PID history arrays'
2026-04-25 implemented best practices
